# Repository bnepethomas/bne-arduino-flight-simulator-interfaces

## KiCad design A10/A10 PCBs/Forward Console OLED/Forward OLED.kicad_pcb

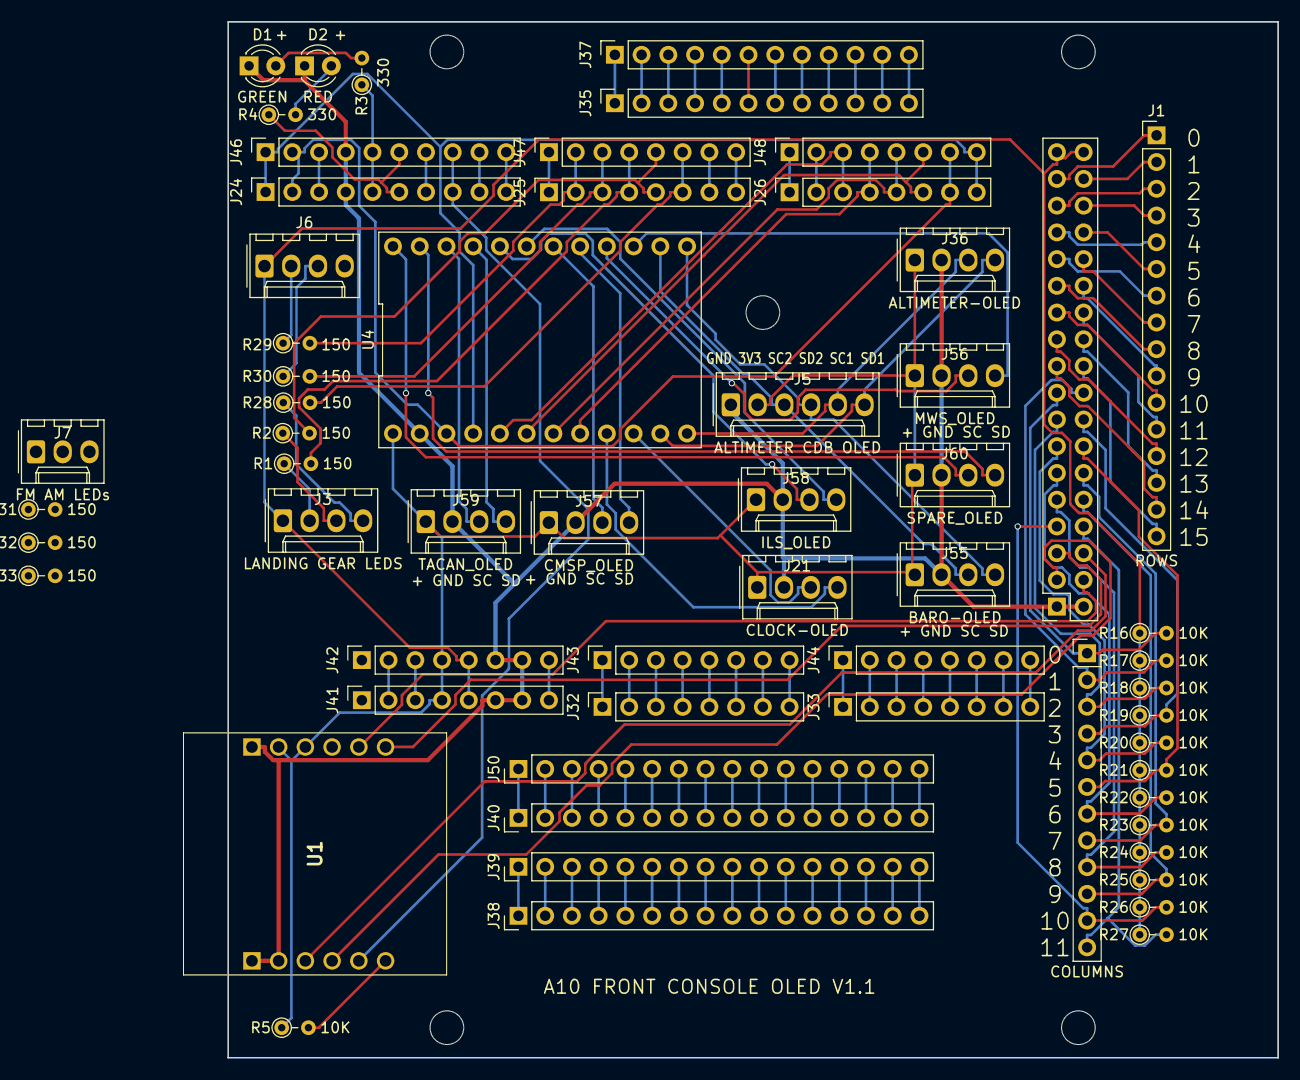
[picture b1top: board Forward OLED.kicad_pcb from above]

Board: 2 copper layers, 99.8 x 98.4 mm, 65 parts (0 on the bottom side), 148 nets.

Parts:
D1: GREEN; LED_D3.0mm
D2: RED; LED_D3.0mm
H1, H2, H3, H4: MountingHole; MountingHole_3.2mm
J1: ROWS; PinHeader_1x16_P2.54mm_Vertical
J2: COLUMNS; PinHeader_1x12_P2.54mm_Vertical
J3: LANDING GEAR LEDS; Molex_KK-254_AE-6410-04A_1x04_P2.54mm_Vertical
J5: ALTIMETER CDB OLED; Molex_KK-254_AE-6410-06A_1x06_P2.54mm_Vertical
J6: AOA LEDs; Molex_KK-254_AE-6410-04A_1x04_P2.54mm_Vertical
J7: FM AM LEDs; Molex_KK-254_AE-6410-03A_1x03_P2.54mm_Vertical
J21: CLOCK-OLED; Molex_KK-254_AE-6410-04A_1x04_P2.54mm_Vertical
J24, J46: PWM; PinSocket_1x10_P2.54mm_Vertical
J25, J47: PWM; PinSocket_1x08_P2.54mm_Vertical
J26, J48: Communication; PinSocket_1x08_P2.54mm_Vertical
J32, J33, J43, J44: Analog; PinSocket_1x08_P2.54mm_Vertical
J35, J37: PATCH; PinSocket_1x12_P2.54mm_Vertical
J36: ALTIMETER-OLED; Molex_KK-254_AE-6410-04A_1x04_P2.54mm_Vertical
J38, J39, J40, J50: PATCH; PinHeader_1x16_P2.54mm_Vertical
J41, J42: Power; PinSocket_1x08_P2.54mm_Vertical
J45: Digital; PinSocket_2x18_P2.54mm_Vertical
J55: BARO-OLED; Molex_KK-254_AE-6410-04A_1x04_P2.54mm_Vertical
J56: MWS_OLED; Molex_KK-254_AE-6410-04A_1x04_P2.54mm_Vertical
J57: CMSP_OLED; Molex_KK-254_AE-6410-04A_1x04_P2.54mm_Vertical
J58: ILS_OLED; Molex_KK-254_AE-6410-04A_1x04_P2.54mm_Vertical
J59: TACAN_OLED; Molex_KK-254_AE-6410-04A_1x04_P2.54mm_Vertical
J60: SPARE_OLED; Molex_KK-254_AE-6410-04A_1x04_P2.54mm_Vertical
MH1: MountingHole_3.2mm
R1, R2, R28, R29, R30, R31, R32, R33: 150; R_Axial_DIN0204_L3.6mm_D1.6mm_P2.54mm_Vertical
R3, R4: 330; R_Axial_DIN0204_L3.6mm_D1.6mm_P2.54mm_Vertical
R5, R16, R17, R18, R19, R20, R21, R22, R23, R24, R25, R26, R27: 10K; R_Axial_DIN0204_L3.6mm_D1.6mm_P2.54mm_Vertical
U1: USR-ES1; USRES1
U4: TCA9548APWR; DIP-24_TCA9548A

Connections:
+3V3: J5.2, J21.1, J36.1, J41.4, J42.4, J55.1, J56.1, J57.1, J58.1, J59.1, J60.1, R5.1, U1.B2 (3V3_1), U1.B3 (3V3_2), U4.1 (VCC)
+5V: J3.1, J6.1, J7.1, J41.5, J42.5, J45.35, J45.36, R16.1, R17.1, R18.1, R19.1, R20.1, R21.1, R22.1, R23.1, R24.1, R25.1, R26.1, R27.1
/*12: J24.6, J46.6, R4.1
/*13: J24.5, J46.5, R3.1
/AREF: J24.3, J46.3
/IOREF: J41.2, J42.2
/OLED/SC0: J21.3, U4.10 (SC0)
/OLED/SC1: J5.5, J36.3, U4.12 (SC1)
/OLED/SC2: J5.3, J55.3, U4.14 (SC2)
/OLED/SC3: J56.3, U4.16 (SC3)
/OLED/SC4: J57.3, U4.18 (SC4)
/OLED/SC5: J58.3, U4.20 (SC5)
/OLED/SC6: J59.3, U4.22 (SC6)
/OLED/SC7: J60.3, U4.24 (SC7)
/OLED/SD0: J21.4, U4.9 (SD0)
/OLED/SD1: J5.6, J36.4, U4.11 (SD1)
/OLED/SD2: J5.4, J55.4, U4.13 (SD2)
/OLED/SD3: J56.4, U4.15 (SD3)
/OLED/SD4: J57.4, U4.17 (SD4)
/OLED/SD5: J58.4, U4.19 (SD5)
/OLED/SD6: J59.4, U4.21 (SD6)
/OLED/SD7: J60.4, U4.23 (SD7)
/RX0/0: J25.8, J47.8
/TX0/1: J25.7, J47.7
/~RESET: J41.3, J42.3
A0 D54: J32.1, J43.1
A1 D55: J32.2, J43.2
A2 D56: J32.3, J43.3
A3 D57: J32.4, J43.4
A4 D58: J32.5, J43.5
A5 D59: J32.6, J43.6
A6 D60: J32.7, J43.7
A7 D61: J32.8, J43.8
A8 D62: J33.1, J44.1
A9 D63: J33.2, J44.2
A10 D64: J33.3, J44.3
A11 D65: J33.4, J44.4
A12 D66: J33.5, J44.5
A13 D67: J33.6, J44.6
A14 D68: J33.7, J44.7
A15 D69: J33.8, J44.8
BACKLIGHT: J25.6, J47.6, R28.2
D3: J25.5, J47.5, R2.2
D4: J25.4, J47.4, R1.2
D5: J25.3, J47.3, R30.2
D6: J25.2, J47.2, R29.2
D7: J25.1, J47.1, R33.2
D8: J24.10, J46.10, R32.2
D9: J24.9, J46.9, R31.2
D11: J24.7, J46.7
D14: J26.1, J48.1
D15: J26.2, J48.2
D16: J26.3, J48.3, U4.5 (~RESET)
D17: J26.4, J48.4, U4.8 (A2)
D18: J26.5, J48.5, U4.7 (A1)
D19: J26.6, J48.6, U4.6 (A0)
D20 SDA: J24.2, J26.7, J46.2, J48.7, U4.3 (SDA)
D21 SCL: J24.1, J26.8, J46.1, J48.8, U4.4 (SCL)
D22: J1.1, J45.33
D23: J1.2, J45.34
D24: J1.3, J45.31
D25: J1.4, J45.32
D26: J1.5, J45.29
D27: J1.6, J45.30
D28: J1.7, J45.27
D29: J1.8, J45.28
D30: J1.9, J45.25
D31: J1.10, J45.26
D32: J1.11, J45.23
D33: J1.12, J45.24
D34: J1.13, J45.21
D35: J1.14, J45.22
D36: J1.15, J45.19
D37: J1.16, J45.20
D38: J2.1, J45.17, R16.2
D39: J2.2, J45.18, R17.2
D40: J2.3, J45.15, R18.2
D41: J2.4, J45.16, R19.2
D42: J2.5, J45.13, R20.2
D43: J2.6, J45.14, R21.2
D44: J2.7, J45.11, R22.2
D45: J2.8, J45.12, R23.2
D46: J2.9, J45.9, R24.2
D47: J2.10, J45.10, R25.2
D48: J2.11, J45.7, R26.2
D49: J2.12, J45.8, R27.2
ES1_RST: J45.4, U1.B5 (RST)
GND: D1.1 (K), D2.1 (K), J5.1, J21.2, J24.4, J36.2, J41.6, J41.7, J42.6, J42.7, J45.1, J45.2, J46.4, J55.2, J56.2, J57.2, J58.2, J59.2, J60.2, U1.A1 (GND_1), U1.A2 (GND_2), U1.B1 (GND_3), U4.2 (GND)
MISO: J45.5, U1.B6 (MISO)
MOSI: J45.6, U1.A3 (MOSI)
unnamed: D1.2 (A), R3.2
unnamed: D2.2 (A), R4.2
unnamed: J3.2, R1.1
unnamed: J3.3, R2.1
unnamed: J3.4, R28.1
unnamed: J6.2, R31.1
unnamed: J6.3, R32.1
unnamed: J6.4, R33.1
unnamed: J7.2, R29.1
unnamed: J7.3, R30.1
unnamed: J35.1, J37.1
unnamed: J35.2, J37.2
unnamed: J35.3, J37.3
unnamed: J35.4, J37.4
unnamed: J35.5, J37.5
unnamed: J35.6, J37.6
unnamed: J35.7, J37.7
unnamed: J35.8, J37.8
unnamed: J35.9, J37.9
unnamed: J35.10, J37.10
unnamed: J35.11, J37.11
unnamed: J35.12, J37.12
unnamed: J38.1, J39.1
unnamed: J38.2, J39.2
unnamed: J38.3, J39.3
unnamed: J38.4, J39.4
unnamed: J38.5, J39.5
unnamed: J38.6, J39.6
unnamed: J38.7, J39.7
unnamed: J38.8, J39.8
unnamed: J38.9, J39.9
unnamed: J38.10, J39.10
unnamed: J38.11, J39.11
unnamed: J38.12, J39.12
unnamed: J38.13, J39.13
unnamed: J38.14, J39.14
unnamed: J38.15, J39.15
unnamed: J38.16, J39.16
unnamed: J40.1, J50.1
unnamed: J40.2, J50.2
unnamed: J40.3, J50.3
unnamed: J40.4, J50.4
unnamed: J40.5, J50.5
unnamed: J40.6, J50.6
unnamed: J40.7, J50.7
unnamed: J40.8, J50.8
unnamed: J40.9, J50.9
unnamed: J40.10, J50.10
unnamed: J40.11, J50.11
unnamed: J40.12, J50.12
unnamed: J40.13, J50.13
unnamed: J40.14, J50.14
unnamed: J40.15, J50.15
unnamed: J40.16, J50.16
unnamed: R5.2, U1.A6 (INT)
SCLK: J45.3, U1.A4 (SCLK)
SS: J24.8, J46.8, U1.A5 (CS)
VCC: J41.8, J42.8

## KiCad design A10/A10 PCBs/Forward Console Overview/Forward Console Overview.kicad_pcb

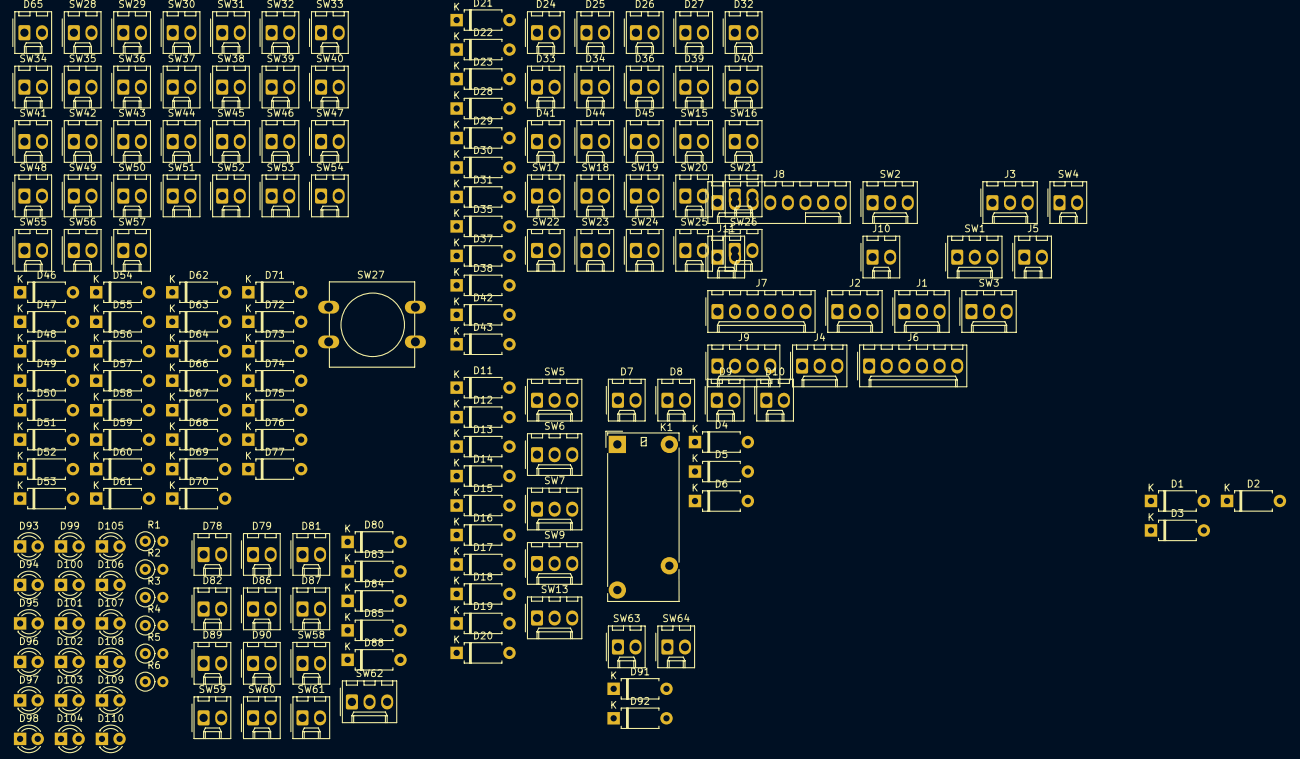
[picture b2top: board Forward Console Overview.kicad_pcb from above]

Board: 2 copper layers, 187 parts (0 on the bottom side), 119 nets, no tracks yet.

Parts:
D1, D2, D3, D4, D5, D6, D11, D12, D13, D14, D15, D16, D17, D18, D19, D20, D21, D22, D23, D28, D29, D30, D31, D35, D37, D38, D42, D43, D46, D47, D48, D49, D50, D51, D52, D53, D54, D55, D56, D57, D58, D59, D60, D61, D62, D63, D64, D66, D67, D68, D69, D70, D71, D72, D73, D74, D75, D76, D77, D80, D83, D84, D85, D88, D91, D92: D; D_A-405_P7.62mm_Horizontal
D7, D8, D9, D10: LED; Molex_KK-254_AE-6410-02A_1x02_P2.54mm_Vertical
D24: PRI; Molex_KK-254_AE-6410-02A_1x02_P2.54mm_Vertical
D25: HARS; Molex_KK-254_AE-6410-02A_1x02_P2.54mm_Vertical
D26: STR PT; Molex_KK-254_AE-6410-02A_1x02_P2.54mm_Vertical
D27: VHF; Molex_KK-254_AE-6410-02A_1x02_P2.54mm_Vertical
D32: SEP; Molex_KK-254_AE-6410-02A_1x02_P2.54mm_Vertical
D33: MISSLE LAUNCH; Molex_KK-254_AE-6410-02A_1x02_P2.54mm_Vertical
D34: ANCHR; Molex_KK-254_AE-6410-02A_1x02_P2.54mm_Vertical
D36: SPARE; Molex_KK-254_AE-6410-02A_1x02_P2.54mm_Vertical
D39: EGI; Molex_KK-254_AE-6410-02A_1x02_P2.54mm_Vertical
D40: TCN; Molex_KK-254_AE-6410-02A_1x02_P2.54mm_Vertical
D41: UHF; Molex_KK-254_AE-6410-02A_1x02_P2.54mm_Vertical
D44: TISL; Molex_KK-254_AE-6410-02A_1x02_P2.54mm_Vertical
D45: ILS; Molex_KK-254_AE-6410-02A_1x02_P2.54mm_Vertical
D65: MASTER CAUTION; Molex_KK-254_AE-6410-02A_1x02_P2.54mm_Vertical
D78: GUN READY A; Molex_KK-254_AE-6410-02A_1x02_P2.54mm_Vertical
D79: GUN READY B; Molex_KK-254_AE-6410-02A_1x02_P2.54mm_Vertical
D81: STEERING A; Molex_KK-254_AE-6410-02A_1x02_P2.54mm_Vertical
D82: STEERING B; Molex_KK-254_AE-6410-02A_1x02_P2.54mm_Vertical
D86: MKR BEACON A; Molex_KK-254_AE-6410-02A_1x02_P2.54mm_Vertical
D87: MKR BEACON B; Molex_KK-254_AE-6410-02A_1x02_P2.54mm_Vertical
D89: CANOPY UNLOCKED A; Molex_KK-254_AE-6410-02A_1x02_P2.54mm_Vertical
D90: CANOPY UNLOCKED B; Molex_KK-254_AE-6410-02A_1x02_P2.54mm_Vertical
D93, D94, D95, D96, D97, D98, D99, D100, D101, D102, D103, D104, D105, D106, D107, D108, D109, D110: LED; LED_D3.0mm_FlatTop
J1, J2, J3, J4: Conn_01x03_Female; Molex_KK-254_AE-6410-03A_1x03_P2.54mm_Vertical
J5: Conn_01x02_Socket; Molex_KK-254_AE-6410-02A_1x02_P2.54mm_Vertical
J6: UFC COLS; Molex_KK-254_AE-6410-06A_1x06_P2.54mm_Vertical
J7: UFC ROWS; Molex_KK-254_AE-6410-06A_1x06_P2.54mm_Vertical
J8: Conn_01x08_Female; Molex_KK-254_AE-6410-08A_1x08_P2.54mm_Vertical
J9: I2C In; Molex_KK-254_AE-6410-04A_1x04_P2.54mm_Vertical
J10, J11: BKLGHT; Molex_KK-254_AE-6410-02A_1x02_P2.54mm_Vertical
K1: ANIT-SKID; Relay_1P1T_NO_10x24x18.8mm_Panasonic_ADW11xxxxW_THT
R1, R2, R3, R4, R5, R6: R_US; R_Axial_DIN0207_L6.3mm_D2.5mm_P2.54mm_Vertical
SW1: FLAPS; Molex_KK-254_AE-6410-03A_1x03_P2.54mm_Vertical
SW2: LANDING LIGHTS; Molex_KK-254_AE-6410-03A_1x03_P2.54mm_Vertical
SW3: BRAKE; Molex_KK-254_AE-6410-03A_1x03_P2.54mm_Vertical
SW4: Encoder_Push; Molex_KK-254_AE-6410-02A_1x02_P2.54mm_Vertical
SW5: MASTER ARM; Molex_KK-254_AE-6410-03A_1x03_P2.54mm_Vertical
SW6: LASER; Molex_KK-254_AE-6410-03A_1x03_P2.54mm_Vertical
SW7: ALT SCE; Molex_KK-254_AE-6410-03A_1x03_P2.54mm_Vertical
SW9: GUM / PAC; Molex_KK-254_AE-6410-03A_1x03_P2.54mm_Vertical
SW13: IFCC; Molex_KK-254_AE-6410-03A_1x03_P2.54mm_Vertical
SW15: PRI; Molex_KK-254_AE-6410-02A_1x02_P2.54mm_Vertical
SW16: HARS; Molex_KK-254_AE-6410-02A_1x02_P2.54mm_Vertical
SW17: STR PT; Molex_KK-254_AE-6410-02A_1x02_P2.54mm_Vertical
SW18: SEP; Molex_KK-254_AE-6410-02A_1x02_P2.54mm_Vertical
SW19: PTR; Molex_KK-254_AE-6410-02A_1x02_P2.54mm_Vertical
SW20: MISSLE LAUNCH; Molex_KK-254_AE-6410-02A_1x02_P2.54mm_Vertical
SW21, SW59, SW60, SW61: ANCHR; Molex_KK-254_AE-6410-02A_1x02_P2.54mm_Vertical
SW22: SPARE; Molex_KK-254_AE-6410-02A_1x02_P2.54mm_Vertical
SW23: EGI; Molex_KK-254_AE-6410-02A_1x02_P2.54mm_Vertical
SW24: TCN; Molex_KK-254_AE-6410-02A_1x02_P2.54mm_Vertical
SW25: TISL; Molex_KK-254_AE-6410-02A_1x02_P2.54mm_Vertical
SW26: ILS; Molex_KK-254_AE-6410-02A_1x02_P2.54mm_Vertical
SW27: STEER +; SW_PUSH-12mm
SW28: STEER -; Molex_KK-254_AE-6410-02A_1x02_P2.54mm_Vertical
SW29: 1; Molex_KK-254_AE-6410-02A_1x02_P2.54mm_Vertical
SW30: 4; Molex_KK-254_AE-6410-02A_1x02_P2.54mm_Vertical
SW31: 7; Molex_KK-254_AE-6410-02A_1x02_P2.54mm_Vertical
SW32: FUNC; Molex_KK-254_AE-6410-02A_1x02_P2.54mm_Vertical
SW33: LTR; Molex_KK-254_AE-6410-02A_1x02_P2.54mm_Vertical
SW34: CLR; Molex_KK-254_AE-6410-02A_1x02_P2.54mm_Vertical
SW35: 2; Molex_KK-254_AE-6410-02A_1x02_P2.54mm_Vertical
SW36: 5; Molex_KK-254_AE-6410-02A_1x02_P2.54mm_Vertical
SW37: 8; Molex_KK-254_AE-6410-02A_1x02_P2.54mm_Vertical
SW38: ENT; Molex_KK-254_AE-6410-02A_1x02_P2.54mm_Vertical
SW39: MK; Molex_KK-254_AE-6410-02A_1x02_P2.54mm_Vertical
SW40: 3; Molex_KK-254_AE-6410-02A_1x02_P2.54mm_Vertical
SW41: 6; Molex_KK-254_AE-6410-02A_1x02_P2.54mm_Vertical
SW42: 9; Molex_KK-254_AE-6410-02A_1x02_P2.54mm_Vertical
SW43, SW45, SW50: INTEN LEFT; Molex_KK-254_AE-6410-02A_1x02_P2.54mm_Vertical
SW44: MASTER CAUTION; Molex_KK-254_AE-6410-02A_1x02_P2.54mm_Vertical
SW46: POS; Molex_KK-254_AE-6410-02A_1x02_P2.54mm_Vertical
SW47: 0; Molex_KK-254_AE-6410-02A_1x02_P2.54mm_Vertical
SW48: SPC; Molex_KK-254_AE-6410-02A_1x02_P2.54mm_Vertical
SW49, SW53: INTEN RIGHT; Molex_KK-254_AE-6410-02A_1x02_P2.54mm_Vertical
SW51: DATA UP; Molex_KK-254_AE-6410-02A_1x02_P2.54mm_Vertical
SW52: DATA DOWN; Molex_KK-254_AE-6410-02A_1x02_P2.54mm_Vertical
SW54: SEL UP; Molex_KK-254_AE-6410-02A_1x02_P2.54mm_Vertical
SW55: SEL DOWN; Molex_KK-254_AE-6410-02A_1x02_P2.54mm_Vertical
SW56: DEPR UP; Molex_KK-254_AE-6410-02A_1x02_P2.54mm_Vertical
SW57: DEPR DOWN; Molex_KK-254_AE-6410-02A_1x02_P2.54mm_Vertical
SW58: EXT STORES JET; Molex_KK-254_AE-6410-02A_1x02_P2.54mm_Vertical
SW62: FIRE EXT DISC; Molex_KK-254_AE-6410-03A_1x03_P2.54mm_Vertical
SW63: JAMMER; Molex_KK-254_AE-6410-02A_1x02_P2.54mm_Vertical
SW64: MWS; Molex_KK-254_AE-6410-02A_1x02_P2.54mm_Vertical

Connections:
/FIRE HANDLES/COL2: D80.2 (A), D84.2 (A), D88.2 (A)
/FIRE HANDLES/COL3: D83.2 (A), D85.2 (A)
/FIRE HANDLES/ROW10: SW58.2, SW59.2
/FIRE HANDLES/ROW11: SW60.2, SW61.2
/JAMMER/ROW14: SW63.2, SW64.2
/LANDING GEAR/COIL_28V: D3.1 (K), K1.1
/LANDING GEAR/COIL_ANTI_SKID: D3.2 (A), K1.6
/LANDING GEAR/COL0: D1.2 (A), D2.2 (A)
/LANDING GEAR/COL1: D4.2 (A), D5.2 (A), D6.2 (A)
/LANDING GEAR/ROW10: SW1.1, SW3.1
/LANDING GEAR/ROW11: SW1.3, SW3.3
/LANDING GEAR/ROW13: K1.3, SW2.3
/MASTER ARM/COL0: D11.2 (A), D12.2 (A)
/MASTER ARM/COL1: D15.2 (A), D17.2 (A), D18.2 (A)
/MASTER ARM/COL2: D13.2 (A), D14.2 (A), D19.2 (A)
/MASTER ARM/COL3: D16.2 (A), D20.2 (A)
/MASTER ARM/ROW6: SW5.1, SW7.1, SW9.1
/MASTER ARM/ROW7: SW5.3, SW7.3, SW9.3, SW13.1
/MASTER ARM/ROW8: SW6.1, SW13.3
/NMSP CMSP/COL4: D21.2 (A), D22.2 (A), D23.2 (A), D35.2 (A), D37.2 (A), D42.2 (A)
/NMSP CMSP/COL5: D28.2 (A), D29.2 (A), D30.2 (A), D31.2 (A), D38.2 (A), D43.2 (A)
/NMSP CMSP/ROW6: SW15.2, SW18.2
/NMSP CMSP/ROW7: SW20.2, SW22.2
/NMSP CMSP/ROW8: SW16.2, SW19.2 (B)
/NMSP CMSP/ROW9: SW17.2, SW21.2
/NMSP CMSP/ROW10: SW23.2, SW24.2
/NMSP CMSP/ROW11: SW25.2, SW26.2
/UFC/CAUTION_LED+: D65.2 (A), J5.1
/UFC/CAUTION_LED-: D65.1 (K), J5.2
/UFC/COL0: D48.2 (A), D49.2 (A), D50.2 (A), D54.2 (A), D55.2 (A), D56.2 (A), J6.1
/UFC/COL1: D59.2 (A), D60.2 (A), D61.2 (A), D66.2 (A), D67.2 (A), D68.2 (A), J6.2
/UFC/COL2: D46.2 (A), D47.2 (A), D51.2 (A), D52.2 (A), D53.2 (A), D57.2 (A), J6.3
/UFC/COL3: D58.2 (A), D62.2 (A), D63.2 (A), D64.2 (A), D69.2 (A), D71.2 (A), J6.4
/UFC/COL4: D70.2 (A), D72.2 (A), D73.2 (A), D74.2 (A), D75.2 (A), D76.2 (A), J6.5
/UFC/COL5: D77.2 (A), J6.6
/UFC/ROW0: J7.1, SW27.2, SW29.2, SW39.2, SW40.2, SW52.2, SW57.2
/UFC/ROW1: J7.2, SW28.2, SW30.2, SW41.2, SW44.2, SW50.2
/UFC/ROW2: J7.3, SW31.2, SW32.2, SW42.2, SW43.2, SW53.2
/UFC/ROW3: J7.4, SW33.2, SW35.2, SW46.2, SW49.2, SW54.2
/UFC/ROW4: J7.5, SW34.2, SW36.2, SW45.2, SW47.2, SW55.2
/UFC/ROW5: J7.6, SW37.2, SW38.2, SW48.2, SW51.2, SW56.2
/UFC/UFC_BACKLIGHTING/BACKLIGHT_+12V: J10.1, J11.1, R1.1, R2.1, R3.1, R4.1, R5.1, R6.1
/UFC/UFC_BACKLIGHTING/BACKLIGHT_GND: D105.1 (K), D106.1 (K), D107.1 (K), D108.1 (K), D109.1 (K), D110.1 (K), J10.2, J11.2
unnamed: D1.1 (K), SW1.2
unnamed: D2.1 (K), SW2.2
unnamed: D4.1 (K), SW3.2
unnamed: D6.1 (K), K1.5
unnamed: D8.2 (A), D9.2 (A), D10.2 (A)
unnamed: D11.1 (K), SW5.2
unnamed: D12.1 (K), SW6.2
unnamed: D13.1 (K), SW7.2
unnamed: D15.1 (K), SW9.2
unnamed: D20.1 (K), SW13.2
unnamed: D21.1 (K), SW15.1
unnamed: D22.1 (K), SW16.1
unnamed: D23.1 (K), SW17.1
unnamed: D28.1 (K), SW18.1
unnamed: D29.1 (K), SW19.1 (A)
unnamed: D30.1 (K), SW20.1
unnamed: D31.1 (K), SW21.1
unnamed: D35.1 (K), SW22.1
unnamed: D37.1 (K), SW23.1
unnamed: D38.1 (K), SW24.1
unnamed: D42.1 (K), SW25.1
unnamed: D43.1 (K), SW26.1
unnamed: D46.1 (K), SW27.1
unnamed: D47.1 (K), SW28.1
unnamed: D48.1 (K), SW29.1
unnamed: D49.1 (K), SW30.1
unnamed: D50.1 (K), SW31.1
unnamed: D51.1 (K), SW32.1
unnamed: D52.1 (K), SW33.1
unnamed: D53.1 (K), SW34.1
unnamed: D54.1 (K), SW35.1
unnamed: D55.1 (K), SW36.1
unnamed: D56.1 (K), SW37.1
unnamed: D57.1 (K), SW38.1
unnamed: D59.1 (K), SW40.1
unnamed: D60.1 (K), SW41.1
unnamed: D61.1 (K), SW42.1
unnamed: D62.1 (K), SW43.1
unnamed: D63.1 (K), SW44.1
unnamed: D64.1 (K), SW45.1
unnamed: D66.1 (K), SW46.1
unnamed: D67.1 (K), SW47.1
unnamed: D68.1 (K), SW48.1
unnamed: D69.1 (K), SW49.1
unnamed: D70.1 (K), SW50.1
unnamed: D72.1 (K), SW52.1
unnamed: D73.1 (K), SW53.1
unnamed: D74.1 (K), SW54.1
unnamed: D75.1 (K), SW55.1
unnamed: D76.1 (K), SW56.1
unnamed: D77.1 (K), SW57.1
unnamed: D80.1 (K), SW58.1
unnamed: D83.1 (K), SW59.1
unnamed: D84.1 (K), SW60.1
unnamed: D85.1 (K), SW61.1
unnamed: D88.1 (K), SW62.2
unnamed: D91.1 (K), SW63.1
unnamed: D92.1 (K), SW64.1
unnamed: D93.2 (A), R1.2
unnamed: D93.1 (K), D99.2 (A)
unnamed: D94.2 (A), R2.2
unnamed: D95.2 (A), R3.2
unnamed: D96.2 (A), R4.2
unnamed: D97.2 (A), R5.2
unnamed: D98.2 (A), R6.2
unnamed: D94.1 (K), D100.2 (A)
unnamed: D100.1 (K), D106.2 (A)
unnamed: D95.1 (K), D101.2 (A)
unnamed: D101.1 (K), D107.2 (A)
unnamed: D96.1 (K), D102.2 (A)
unnamed: D102.1 (K), D108.2 (A)
unnamed: D97.1 (K), D103.2 (A)
unnamed: D103.1 (K), D109.2 (A)
unnamed: D98.1 (K), D104.2 (A)
unnamed: D104.1 (K), D110.2 (A)
unnamed: D99.1 (K), D105.2 (A)

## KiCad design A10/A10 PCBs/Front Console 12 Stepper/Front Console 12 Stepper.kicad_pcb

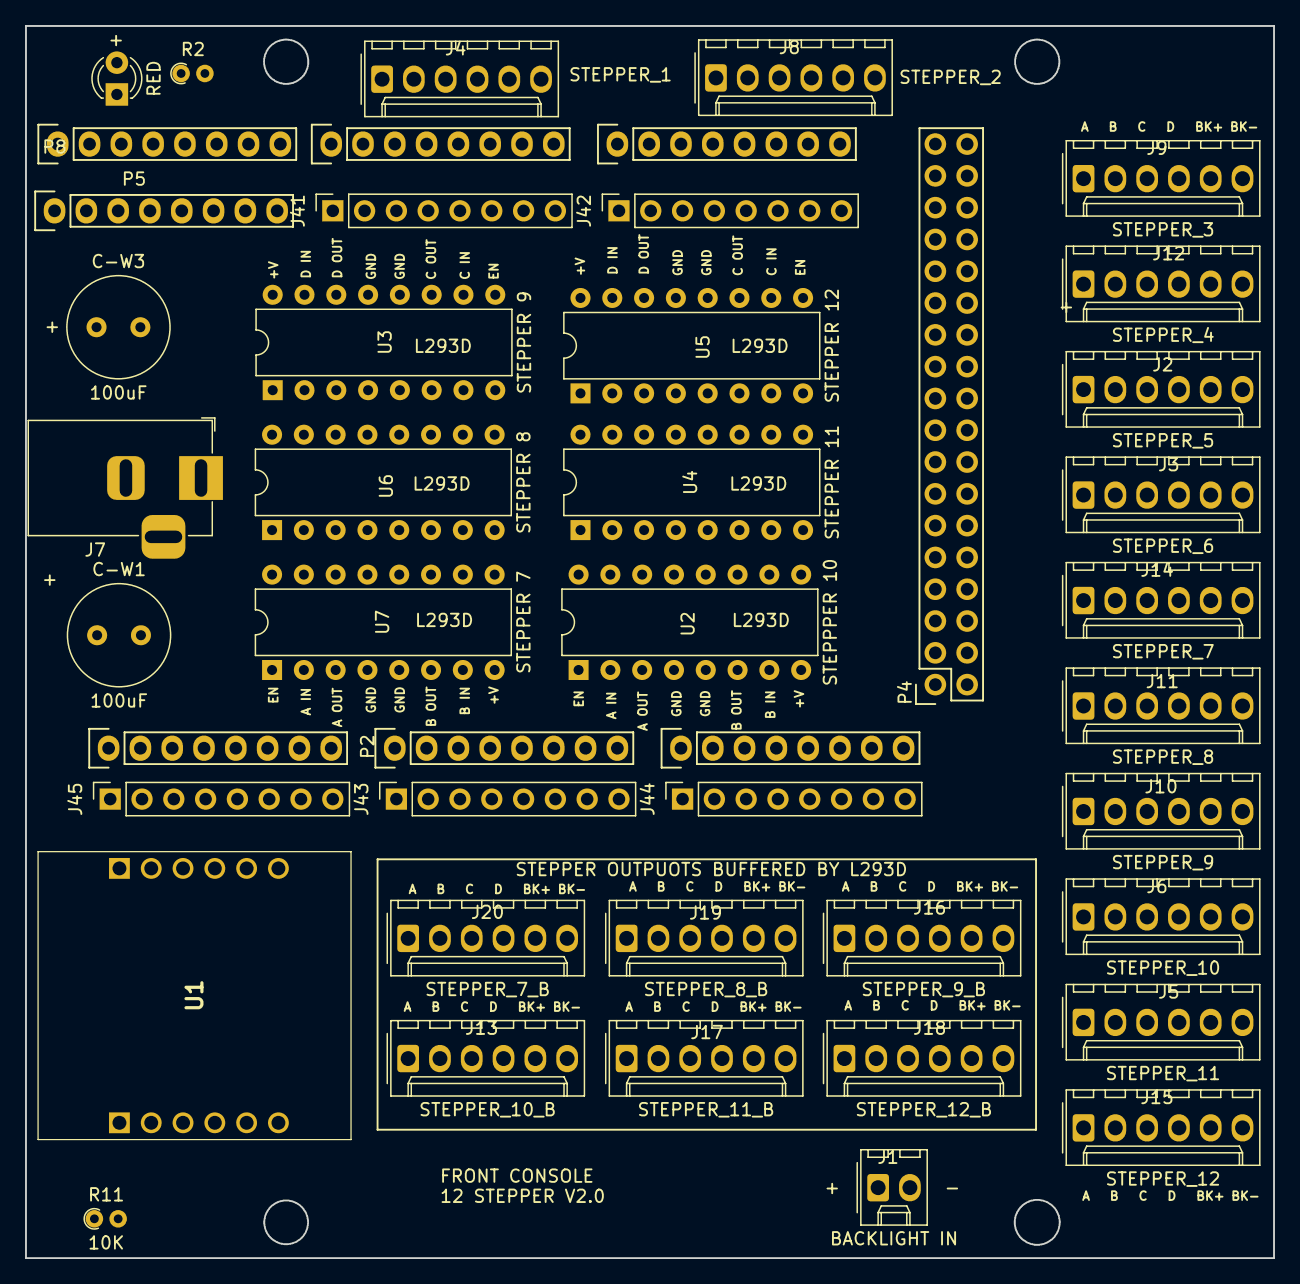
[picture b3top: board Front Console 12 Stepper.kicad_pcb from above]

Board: 2 copper layers, 99.7 x 98.4 mm, 45 parts (0 on the bottom side), 107 nets, no tracks yet.

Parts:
C-W1, C-W3: 100uF; C_Radial_D8.0mm_H7.0mm_P3.50mm
D2: RED; LED_D3.0mm
J1: BACKLIGHT IN; Molex_KK-254_AE-6410-02A_1x02_P2.54mm_Vertical
J2: STEPPER_5; Molex_KK-254_AE-6410-06A_1x06_P2.54mm_Vertical
J3: STEPPER_6; Molex_KK-254_AE-6410-06A_1x06_P2.54mm_Vertical
J4: STEPPER_1; Molex_KK-254_AE-6410-06A_1x06_P2.54mm_Vertical
J5: STEPPER_11; Molex_KK-254_AE-6410-06A_1x06_P2.54mm_Vertical
J6: STEPPER_10; Molex_KK-254_AE-6410-06A_1x06_P2.54mm_Vertical
J7: STEPPER 5V; BarrelJack_Horizontal
J8: STEPPER_2; Molex_KK-254_AE-6410-06A_1x06_P2.54mm_Vertical
J9: STEPPER_3; Molex_KK-254_AE-6410-06A_1x06_P2.54mm_Vertical
J10: STEPPER_9; Molex_KK-254_AE-6410-06A_1x06_P2.54mm_Vertical
J11: STEPPER_8; Molex_KK-254_AE-6410-06A_1x06_P2.54mm_Vertical
J12: STEPPER_4; Molex_KK-254_AE-6410-06A_1x06_P2.54mm_Vertical
J13: STEPPER_10_B; Molex_KK-254_AE-6410-06A_1x06_P2.54mm_Vertical
J14: STEPPER_7; Molex_KK-254_AE-6410-06A_1x06_P2.54mm_Vertical
J15: STEPPER_12; Molex_KK-254_AE-6410-06A_1x06_P2.54mm_Vertical
J16: STEPPER_9_B; Molex_KK-254_AE-6410-06A_1x06_P2.54mm_Vertical
J17: STEPPER_11_B; Molex_KK-254_AE-6410-06A_1x06_P2.54mm_Vertical
J18: STEPPER_12_B; Molex_KK-254_AE-6410-06A_1x06_P2.54mm_Vertical
J19: STEPPER_8_B; Molex_KK-254_AE-6410-06A_1x06_P2.54mm_Vertical
J20: STEPPER_7_B; Molex_KK-254_AE-6410-06A_1x06_P2.54mm_Vertical
J41: PWM; PinSocket_1x08_P2.54mm_Vertical
J42: Communication; PinSocket_1x08_P2.54mm_Vertical
J43, J44: Analog; PinSocket_1x08_P2.54mm_Vertical
J45: Power; PinSocket_1x08_P2.54mm_Vertical
P1: Power; Socket_Strip_Arduino_1x08
P2, P3: Analog; Socket_Strip_Arduino_1x08
P4: Digital; Socket_Strip_Arduino_2x18
P5, P6, P8: PWM; Socket_Strip_Arduino_1x08
P7: Communication; Socket_Strip_Arduino_1x08
R2: 330; R_Axial_DIN0204_L3.6mm_D1.6mm_P1.90mm_Vertical
R11: 10K; R_Axial_DIN0204_L3.6mm_D1.6mm_P1.90mm_Vertical
U1: USR-ES1; USRES1
U2: STEPPPER 10; DIP-16_W7.62mm
U3: STEPPER 9; DIP-16_W7.62mm
U4: STEPPER 11; DIP-16_W7.62mm
U5: STEPPER 12; DIP-16_W7.62mm
U6: STEPPER 8; DIP-16_W7.62mm
U7: STEPPER 7; DIP-16_W7.62mm

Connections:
+3V3: J45.4, P1.4, R11.1, U1.B2 (3V3_1), U1.B3 (3V3_2)
+5VL: C-W1.1, C-W3.1, J45.5, P1.5, U2.1 (EN1,2), U2.9 (EN3,4), U3.1 (EN1,2), U3.9 (EN3,4), U4.1 (EN1,2), U4.9 (EN3,4), U5.1 (EN1,2), U5.9 (EN3,4), U6.1 (EN1,2), U6.9 (EN3,4), U7.1 (EN1,2), U7.9 (EN3,4)
/*2: J41.6, P6.6
/*3: J41.5, P6.5
/*4: J8.4, J41.4, P6.4
/*5: J8.3, J41.3, P6.3
/*6: J8.2, J41.2, P6.2
/*7: J8.1, J41.1, P6.1
/*8: P5.8, P8.8, R2.1
/*9: J4.4, P5.7, P8.7
/*11: J4.3, P5.5, P8.5
/*12: J4.2, P5.4, P8.4
/*13: J4.1, P5.3, P8.3
/A0: J9.1, J43.1, P2.1
/A1: J9.2, J43.2, P2.2
/A2: J9.3, J43.3, P2.3
/A3: J9.4, J43.4, P2.4
/A4: J43.5, P2.5
/A5: J43.6, P2.6
/A6: J43.7, P2.7
/A7: J43.8, P2.8
/A8: J44.1, P3.1
/A9: J44.2, P3.2
/A10: J44.3, P3.3
/A11: J44.4, P3.4
/A12: J44.5, P3.5
/A13: J44.6, P3.6
/A14: J44.7, P3.7
/A15: J44.8, P3.8
/AREF: P5.1, P8.1
/IOREF: J45.2, P1.2
/RX0/0: J41.8, P6.8
/RX1/19: J2.2, J42.6, P7.6
/RX2/17: J12.4, J42.4, P7.4
/RX3/15: J12.2, J42.2, P7.2
/Reset: J45.3, P1.3
/SCL/21: J2.4, J42.8, P7.8
/SDA/20: J2.3, J42.7, P7.7
/STEPPER_4_A: J12.1, J42.1, P7.1
/STEPPER_4_C: J12.3, J42.3, P7.3
/STEPPER_5_A: J2.1, J42.5, P7.5
/TX0/1: J41.7, P6.7
BACKLIGHT_LED+: J1.1, J2.5, J3.5, J4.5, J5.5, J6.5, J8.5, J9.5, J10.5, J11.5, J12.5, J13.5, J14.5, J15.5, J16.5, J17.5, J18.5, J19.5, J20.5
BACKLIGHT_LED-: J1.2, J2.6, J3.6, J4.6, J5.6, J6.6, J8.6, J9.6, J10.6, J11.6, J12.6, J13.6, J14.6, J15.6, J16.6, J17.6, J18.6, J19.6, J20.6
ES1_RST: P4.4, U1.B5 (RST)
GND: C-W1.2, C-W3.2, D2.1 (K), J7.2, J45.6, J45.7, P1.6, P1.7, P4.1, P4.2, P5.2, P8.2, U1.A1 (GND_1), U1.A2 (GND_2), U1.B1 (GND_3), U2.4 (GND), U2.5 (GND), U2.12 (GND), U2.13 (GND), U3.4 (GND), U3.5 (GND), U3.12 (GND), U3.13 (GND), U4.4 (GND), U4.5 (GND), U4.12 (GND), U4.13 (GND), U5.4 (GND), U5.5 (GND), U5.12 (GND), U5.13 (GND), U6.4 (GND), U6.5 (GND), U6.12 (GND), U6.13 (GND), U7.4 (GND), U7.5 (GND), U7.12 (GND), U7.13 (GND)
MISO: P4.5, U1.B6 (MISO)
MOSI: P4.6, U1.A3 (MOSI)
unnamed: D2.2 (A), R2.2
unnamed: J13.1, U2.3 (1Y)
unnamed: J13.2, U2.6 (2Y)
unnamed: J13.3, U2.11 (3Y)
unnamed: J13.4, U2.14 (4Y)
unnamed: J16.1, U3.3 (1Y)
unnamed: J16.2, U3.6 (2Y)
unnamed: J16.3, U3.11 (3Y)
unnamed: J16.4, U3.14 (4Y)
unnamed: J17.1, U4.3 (1Y)
unnamed: J17.2, U4.6 (2Y)
unnamed: J17.3, U4.11 (3Y)
unnamed: J17.4, U4.14 (4Y)
unnamed: J18.1, U5.3 (1Y)
unnamed: J18.2, U5.6 (2Y)
unnamed: J18.3, U5.11 (3Y)
unnamed: J18.4, U5.14 (4Y)
unnamed: J19.1, U6.3 (1Y)
unnamed: J19.2, U6.6 (2Y)
unnamed: J19.3, U6.11 (3Y)
unnamed: J19.4, U6.14 (4Y)
unnamed: J20.1, U7.3 (1Y)
unnamed: J20.2, U7.6 (2Y)
unnamed: J20.3, U7.11 (3Y)
unnamed: J20.4, U7.14 (4Y)
unnamed: P4.35, P4.36
unnamed: R11.2, U1.A6 (INT)
SCLK: P4.3, U1.A4 (SCLK)
SS: P5.6, P8.6, U1.A5 (CS)
STEP_V+: J7.1, U2.8 (VCC2), U2.16 (VCC1), U3.8 (VCC2), U3.16 (VCC1), U4.8 (VCC2), U4.16 (VCC1), U5.8 (VCC2), U5.16 (VCC1), U6.8 (VCC2), U6.16 (VCC1), U7.8 (VCC2), U7.16 (VCC1)
STPPER_6_A: J3.4, P4.33
STPPER_6_B: J3.3, P4.31
STPPER_6_C: J3.2, P4.29
STPPER_6_D: J3.1, P4.27
STPPER_7_A: J14.1, P4.25, U7.2 (1A)
STPPER_7_B: J14.2, P4.23, U7.7 (2A)
STPPER_7_C: J14.3, P4.21, U7.10 (3A)
STPPER_7_D: J14.4, P4.19, U7.15 (4A)
STPPER_8_A: J11.1, P4.17, U6.2 (1A)
STPPER_8_B: J11.2, P4.15, U6.7 (2A)
STPPER_8_C: J11.3, P4.13, U6.10 (3A)
STPPER_8_D: J11.4, P4.11, U6.15 (4A)
STPPER_9_A: J10.1, P4.34, U3.2 (1A)
STPPER_9_B: J10.2, P4.32, U3.7 (2A)
STPPER_9_C: J10.3, P4.30, U3.10 (3A)
STPPER_9_D: J10.4, P4.28, U3.15 (4A)
STPPER_10_A: J6.1, P4.26, U2.2 (1A)
STPPER_10_B: J6.2, P4.24, U2.7 (2A)
STPPER_10_C: J6.3, P4.22, U2.10 (3A)
STPPER_10_D: J6.4, P4.20, U2.15 (4A)
STPPER_11_A: J5.1, P4.18, U4.2 (1A)
STPPER_11_B: J5.2, P4.16, U4.7 (2A)
STPPER_11_C: J5.3, P4.14, U4.10 (3A)
STPPER_11_D: J5.4, P4.12, U4.15 (4A)
STPPER_12_A: J15.1, P4.10, U5.2 (1A)
STPPER_12_B: J15.2, P4.8, U5.7 (2A)
STPPER_12_C: J15.3, P4.9, U5.10 (3A)
STPPER_12_D: J15.4, P4.7, U5.15 (4A)
VCC: J45.8, P1.8

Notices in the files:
A10/A10 PCBs/GAUGE_Analog Instruments/GAUGE_Analog Instruments.kicad_pcb:
CC BY-NC-SA
